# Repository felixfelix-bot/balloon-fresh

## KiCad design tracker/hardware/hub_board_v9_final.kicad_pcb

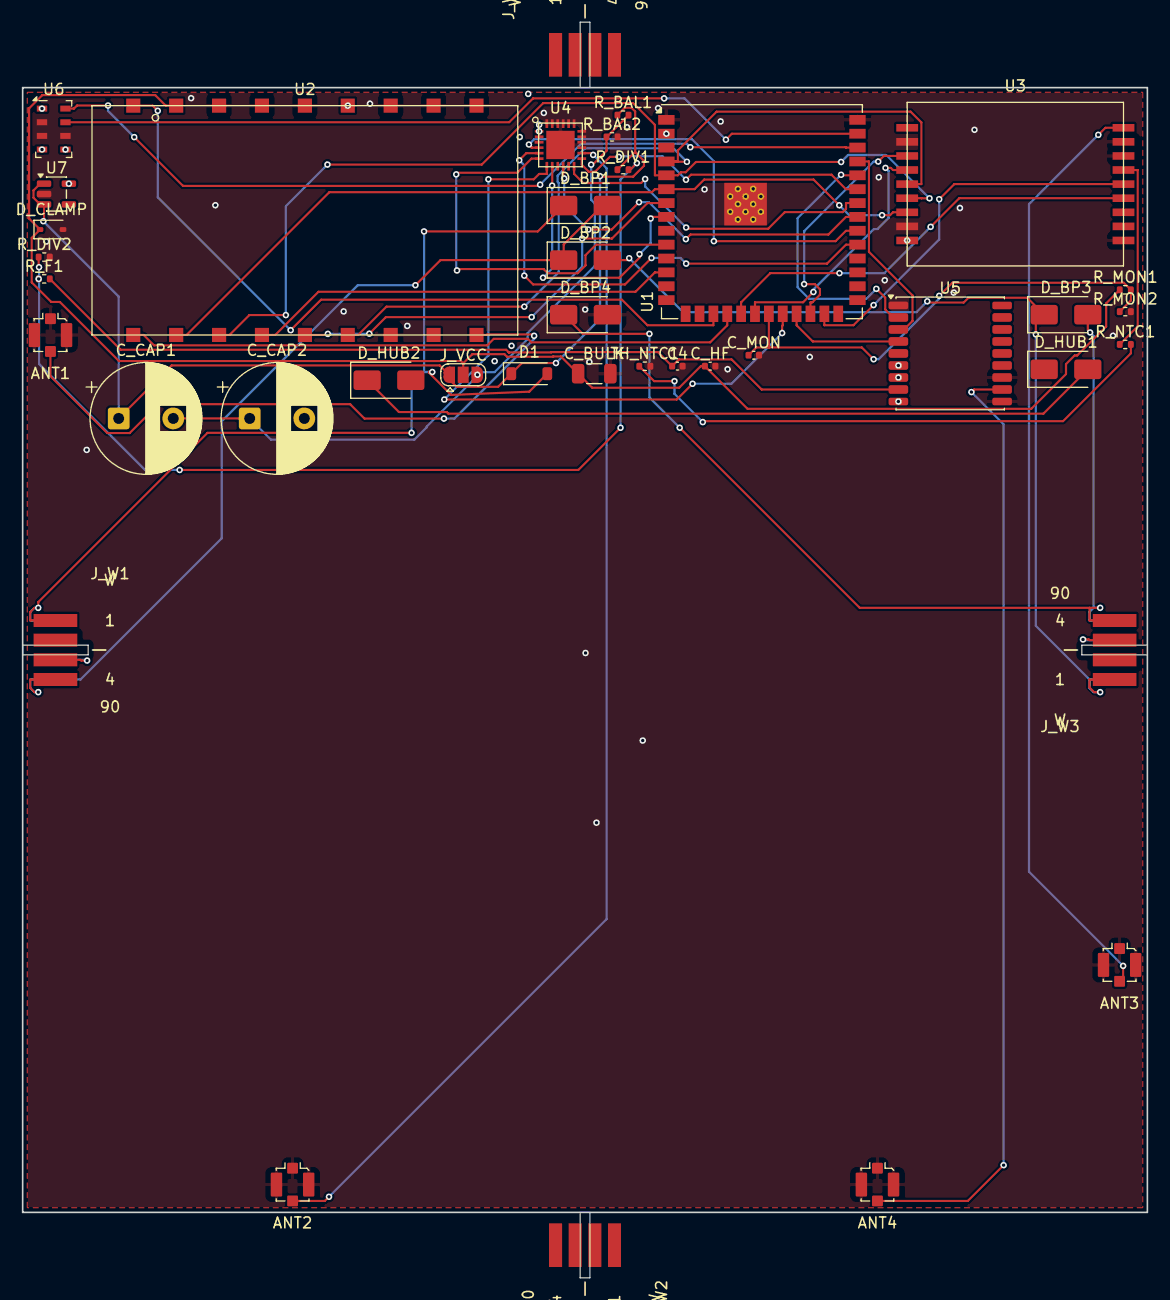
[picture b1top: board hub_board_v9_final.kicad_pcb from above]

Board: 4 copper layers, 103.0 x 103.0 mm, 39 parts (0 on the bottom side), 45 nets.

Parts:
ANT1: U.FL_433_TX; U.FL_Molex_MCRF_73412-0110_Vertical
ANT2: U.FL_2G4_RANGE; U.FL_Molex_MCRF_73412-0110_Vertical
ANT3: U.FL_2G4_RX; U.FL_Molex_MCRF_73412-0110_Vertical
ANT4: U.FL_GNSS_L1; U.FL_Molex_MCRF_73412-0110_Vertical
C4: 10uF; C_0402_1005Metric
C_BULK: 100uF; C_1206_3216Metric
C_CAP1, C_CAP2: 3.3F 2.7V (AVX SCC); CP_Radial_D10.0mm_P5.00mm
C_HF: 100nF; C_0402_1005Metric
C_MON: 10nF; C_0402_1005Metric
D1: BAT54; D_SOD-123
D_BP1, D_BP2, D_BP3, D_BP4: SS24; D_SMA
D_CLAMP: TVS clamp (set point TODO(unverified)); D_SOD-323
D_HUB1, D_HUB2: SS24; D_SMA
J_VCC: F33_VCC_SEL (5V raw | 3V3); SolderJumper-3_P1.3mm_Open_RoundedPad1.0x1.5mm
J_W1: WING_SOCKET_4P (hub wing interface 1); Wing_Tab_4P
J_W2: WING_SOCKET_4P (hub wing interface 2); Wing_Tab_4P
J_W3: WING_SOCKET_4P (hub wing interface 3); Wing_Tab_4P
J_W4: WING_SOCKET_4P (hub wing interface 4); Wing_Tab_4P
R_BAL1, R_BAL2: 10k; R_0402_1005Metric
R_DIV1, R_DIV2: 1M; R_0402_1005Metric
R_F1: 100R; R_0402_1005Metric
R_MON1, R_MON2: 4.7M; R_0402_1005Metric
R_NTC1: TODO(unverified) (sets ntc_r_ratio); R_0402_1005Metric
TH_NTC1: TODO(unverified) (NTC, R25/beta TODO); R_0402_1005Metric
U1: ESP32-S3-WROOM-1U-N8R8; ESP32-S3-WROOM-1U
U2: LoRa2021F33-2G4; LoRa2021F33_2G4
U3: LoRa2021_Castellated
U4: SX1280; SX1280_QFN24
U5: MAX-M10S; ublox_MAX
U6: MS5611-01BA; LGA-8_3x5mm_P1.25mm
U7: TPS7A02; SOT-23-5

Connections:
+3V3: J_VCC.3, R_F1.1, U1.2, U2.5, U3.1, U4.1, U4.2, U5.6, U5.7, U5.9, U6.1, U6.4, U6.5, U7.5
/ANT1_433_TX: ANT1.1, U2.9
/ANT2_2G4_RANGE: ANT2.1, U4.14
/ANT3_2G4_RX: ANT3.1, U3.10
/ANT4_GNSS_L1: ANT4.1, U5.11
/F33_BUSY: U1.12, U2.14
/F33_CS_N: U1.7, U2.13
/F33_IRQ: U1.17, U2.18
/F33_MISO: U1.6, U2.16, U3.3
/F33_MOSI: U1.5, U2.15, U3.4
/F33_RESET_N: U1.18, U2.17
/F33_SCK: U1.4, U2.12, U3.5
/F33_VCC: C_BULK.1, C_HF.1, D_CLAMP.1, J_VCC.2, R_MON1.1, U2.1
/F33_VSENSE: C_MON.1, R_MON1.2, R_MON2.1, U1.21
/GNSS_PPS: U1.23, U5.4
/GNSS_RX: U1.37, U5.3
/GNSS_TX: U1.36, U5.2
/GNSS_VCC: C4.1, R_F1.2, U5.8
/HUB_PV_MID1: D_HUB1.2, D_HUB2.1
/I2C_SCL: U1.38, U6.8
/I2C_SDA: U1.39, U6.7
/NTC_SENSE: R_NTC1.2, TH_NTC1.1
/SCAP_ADC: R_DIV1.2, R_DIV2.1
/SCAP_MID: C_CAP1.2, C_CAP2.1, R_BAL1.2, R_BAL2.1
/SX1280_ANT_SW: U1.35, U4.13
/SX1280_BUSY: U1.31, U4.5
/SX1280_CS_N: U1.10, U4.6
/SX1280_DIO1: U1.33, U4.10
/SX1280_DIO2: U1.11, U4.11
/SX1280_DIO3: U1.34, U4.12
/SX1280_MISO: U1.9, U4.9
/SX1280_MOSI: U1.8, U4.8
/SX1280_RESET_N: U1.32, U4.4
/SX1280_SCK: U1.22, U4.7
/U3_BUSY: U1.24, U3.7
/U3_CS_N: U1.20, U3.6
/U3_IRQ: U1.19, U3.15
/U3_RESET_N: U1.25, U3.14
/VSCAP: C_CAP1.1, D1.1, J_VCC.1, R_BAL1.1, R_DIV1.1, U7.1, U7.3
/VTCXO_VNTC: R_NTC1.1, U3.13
/W1_SOLAR_N: D_BP1.2, D_BP2.1, J_W1.4, J_W2.1
/W1_SOLAR_P: D1.2, D_BP1.1, J_W1.1
/W2_SOLAR_N: D_BP2.2, D_BP3.1, J_W2.4, J_W3.1
/W3_SOLAR_N: D_BP3.2, D_BP4.1, J_W3.4, J_W4.1
GND: ANT1.2, ANT2.2, ANT3.2, ANT4.2, C4.2, C_BULK.2, C_CAP2.2, C_HF.2, C_MON.2, D_BP4.2, D_CLAMP.2, J_W1.2, J_W2.2, J_W3.2, J_W4.2, J_W4.4, R_BAL2.2, R_DIV2.2, R_MON2.2, TH_NTC1.2, U1.1, U1.40, U1.41, U2.2, U2.3, U2.4, U2.6, U2.7, U2.8, U2.11, U3.2, U3.8, U3.11, U3.12, U3.18, U4.3, U4.15, U4.16, U4.17, U4.18, U4.19, U4.20, U4.21, U4.22, U4.23, U4.24, U4.25, U5.1, U5.10, U5.12, U6.2, U6.3, U6.6, U7.2
